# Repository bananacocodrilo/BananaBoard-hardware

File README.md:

# BananaBoard-hardware

This is still under development and subject to changes.

Split wireless keyboard based on the [mitosis](https://github.com/reversebias/mitosis-hardware) and the [chimera](https://github.com/GlenPickle/Chimera).

The goal is to make boards easy to solder and compatible with existing cases for popular keybards as "let's split" or "iris keyboard" and a miniboard for handwired builds.

I'll also publish a fork of their firmware as well since I need to use a matrix configuration instead of a "pin per switch", furthermore I'll add battery measure and underglow leds.

I haven't make a PCB in a while and is my first time using kicad so I'm learning as a I go.

Current state:
-
 - "Finished" schematic: I like how it is right now and it will probably stay like this.
 - "Finished" a first version for handwired builds (it fits in 24mmx50mm so I added 2 per board).
 - Second version of the 40% split PCB, I think is compatible with the "lets split" case but it isn't reversible so I'll need to create the "right hand" too.

Next steps: 
-
 - Decide a footprint for the switches (right now I'm not sure which footprint works with which switch).
 - (Currently working) Create the right hand of the lets split.
 - Investigate other lipo charger circuits. I've ordered a few cheap micro usb ones since I couldn't find reliable size info.
 - Start the firmware modifications.

Ortho 40% board (left hand):

Handwired keyboards board:

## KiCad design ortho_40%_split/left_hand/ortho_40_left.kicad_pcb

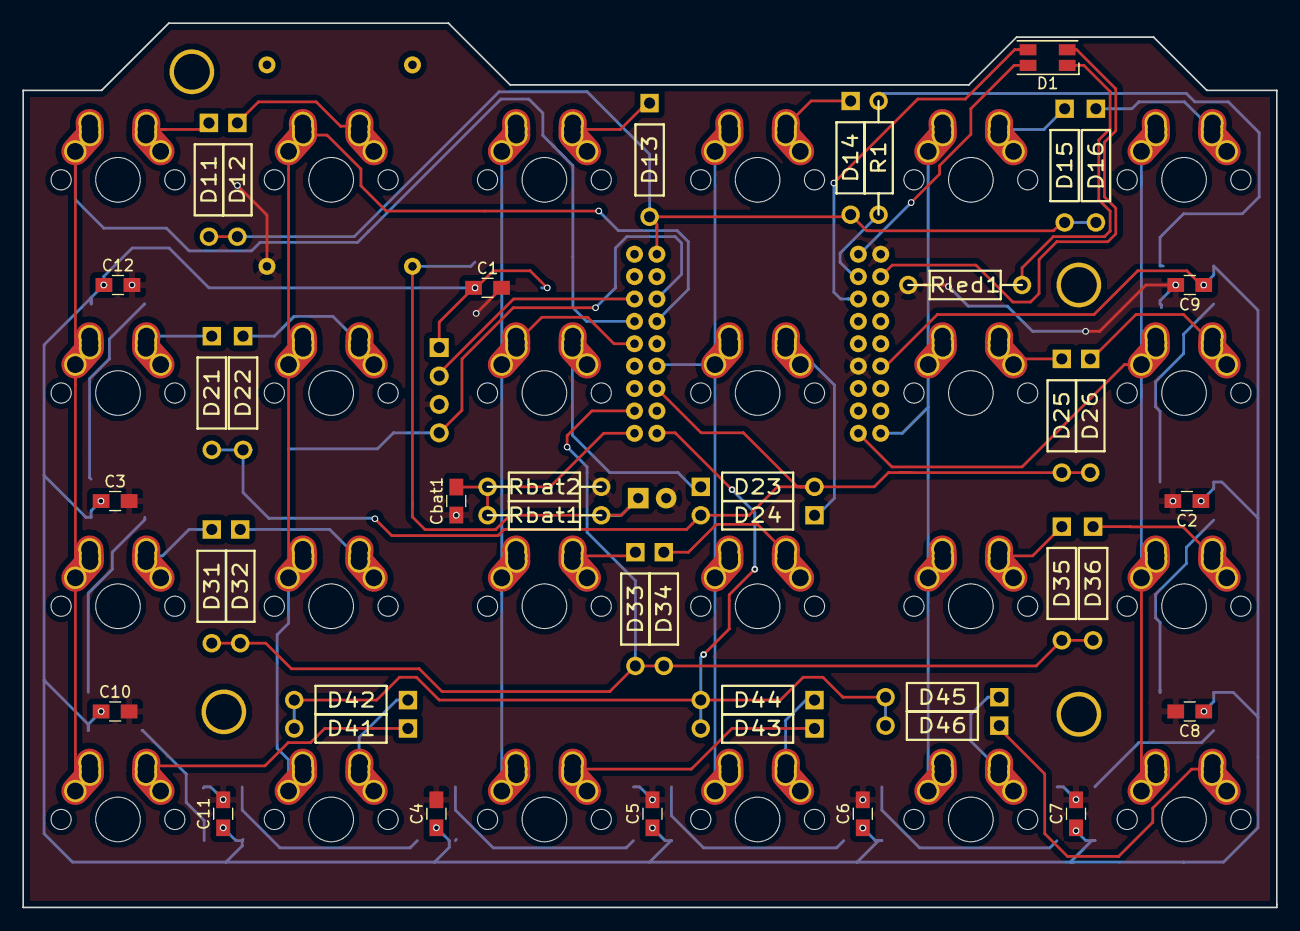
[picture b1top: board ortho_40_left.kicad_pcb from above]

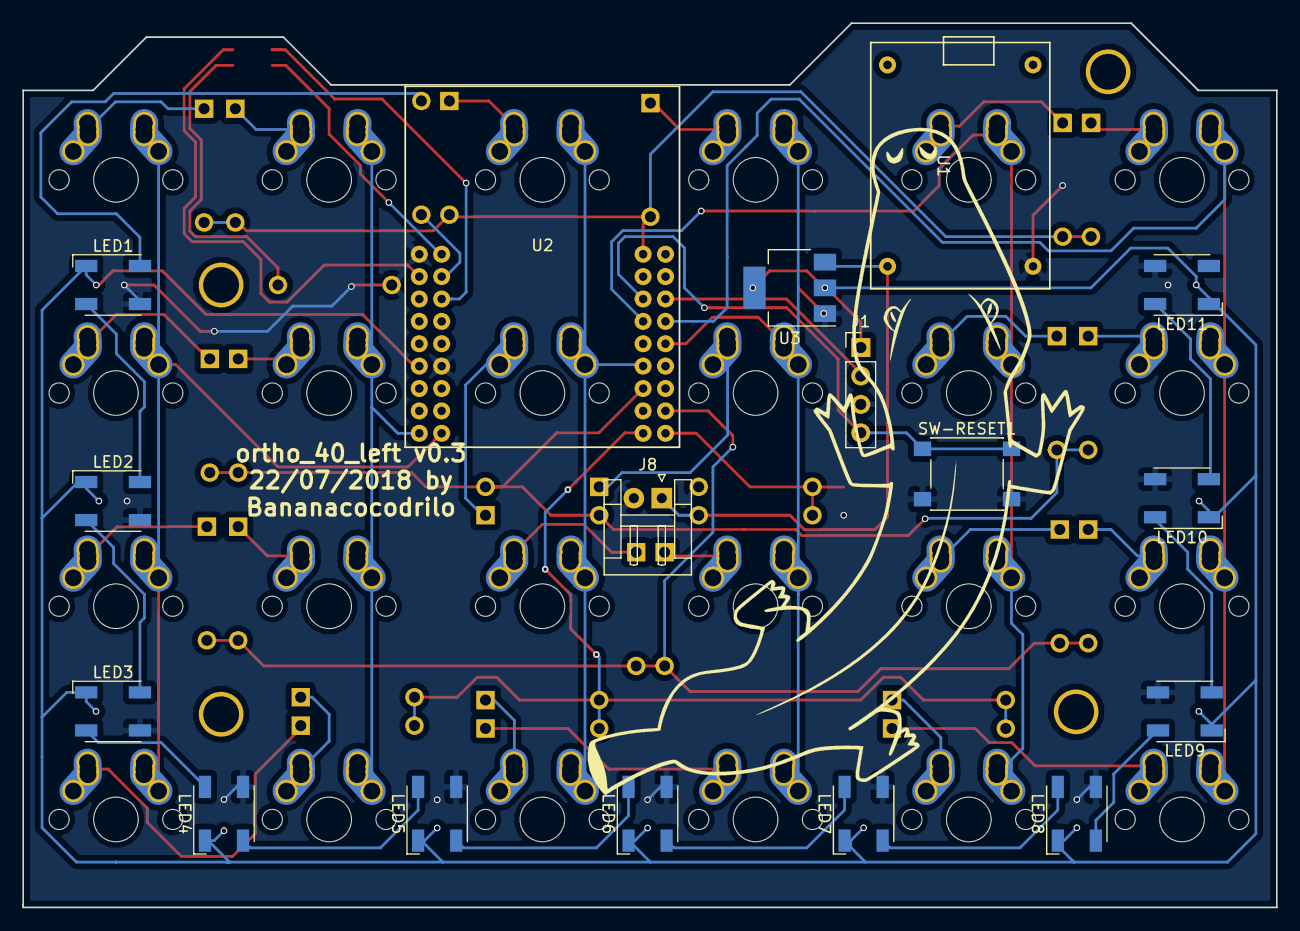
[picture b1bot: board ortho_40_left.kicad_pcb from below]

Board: 2 copper layers, 112.0 x 79.0 mm, 87 parts (17 on the bottom side), 56 nets.

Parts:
C1: 47uF; C_0805_HandSoldering
C2, C3, C4, C5, C6, C7, C8, C9, C10, C11, C12: 0.1uF; C_0805_HandSoldering
Cbat1: 22n; C_0805_HandSoldering
D1: LED_BAT; LED_RGB_1210
D11, D12, D13, D14, D15, D16, D21, D22, D23, D24, D25, D26, D31, D32, D33, D34, D35, D36, D41, D42, D43, D44, D45, D46: D; DIODE
J1: prog_pins; Pin_Header_Straight_1x04_Pitch2.54mm
J2, J3, J5, J7: Conn_01x01; HOLE_M3
J8: Conn-Battery; JST_EH_S02B-EH_02x2.50mm_Angled
K-11, K-12, K-13, K-14, K-15, K-16, K-21, K-22, K-23, K-24, K-25, K-26, K-31, K-32, K-33, K-34, K-35, K-36, K-41, K-42, K-43, K-44, K-45, K-46: KEYSW; Hybrid_PCB_100H_Dual_hole
LED1, LED2, LED3, LED4, LED5, LED6, LED7, LED8, LED9, LED10, LED11: WS2812B; LED_RGB_5050-4
R1: 470; RESISTOR
Rbat1: 10M; RESISTOR
Rbat2: 2.2M; RESISTOR
Rled1: 470; RESISTOR
SW-RESET1: SW_PUSH; SW_SPST_PTS645
U1: cargador-USB; cargador-mini-usb
U2: core51822; core51822-through-hole
U3: LM1117-3.3; SOT-223-3_TabPin2

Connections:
BAT-M: Cbat1.2, Rbat1.1, Rbat2.2, U2.36
GND: C1.2, C2.2, C3.2, C4.2, C5.2, C6.2, C7.2, C8.2, C9.2, C10.2, C11.2, C12.2, Cbat1.1, J1.3, J8.2, LED1.3, LED2.3, LED3.3, LED4.3, LED5.3, LED6.3, LED7.3, LED8.3, LED9.3, LED10.3, LED11.3, Rbat2.1, Rled1.1, SW-RESET1.2, U1.3, U2.1, U2.12, U3.1
LED-B: D1.4, U2.2
LED-G: D1.3, U2.6
LED-R: D1.2, U2.3
unnamed: D1.1, Rled1.2
unnamed: D11.2, K-11.2
unnamed: D12.2, K-12.2
unnamed: D13.2, K-13.2
unnamed: D14.2, K-14.2
unnamed: D15.2, K-15.2
unnamed: D16.2, K-16.2
unnamed: D21.2, K-21.2
unnamed: D22.2, K-22.2
unnamed: D23.2, K-23.2
unnamed: D24.2, K-24.2
unnamed: D25.2, K-25.2
unnamed: D26.2, K-26.2
unnamed: D31.2, K-31.2
unnamed: D32.2, K-32.2
unnamed: D33.2, K-33.2
unnamed: D34.2, K-34.2
unnamed: D35.2, K-35.2
unnamed: D36.2, K-36.2
unnamed: D41.2, K-41.2
unnamed: D42.2, K-42.2
unnamed: D43.2, K-43.2
unnamed: D44.2, K-44.2
unnamed: D45.2, K-45.2
unnamed: D46.2, K-46.2
unnamed: J1.2, U2.24
unnamed: J1.4, SW-RESET1.1, U2.23
unnamed: J8.1, Rbat1.2, U1.2, U3.3
unnamed: LED1.2, LED2.4
unnamed: LED1.4, R1.1
unnamed: LED2.2, LED3.4
unnamed: LED3.2, LED4.4
unnamed: LED4.2, LED5.4
unnamed: LED5.2, LED6.4
unnamed: LED6.2, LED7.4
unnamed: LED7.2, LED8.4
unnamed: LED8.2, LED9.4
unnamed: LED10.2, LED11.4
VCC: C1.1, C2.1, C3.1, C4.1, C5.1, C6.1, C7.1, C8.1, C9.1, C10.1, C11.1, C12.1, J1.1, LED1.1, LED2.1, LED3.1, LED4.1, LED5.1, LED6.1, LED7.1, LED8.1, LED9.1, LED10.1, LED11.1, U2.11, U3.2
col-1: K-11.1, K-21.1, K-31.1, K-41.1, U2.26
col-2: K-12.1, K-22.1, K-32.1, K-42.1, U2.25
col-3: K-13.1, K-23.1, K-33.1, K-43.1, U2.28
col-4: K-14.1, K-24.1, K-34.1, K-44.1, U2.29
col-5: K-15.1, K-25.1, K-35.1, K-45.1, U2.17
col-6: K-16.1, K-26.1, K-36.1, K-46.1, U2.18
row-1: D11.1, D12.1, D13.1, D14.1, D15.1, D16.1, U2.19
row-2: D21.1, D22.1, D23.1, D24.1, D25.1, D26.1, U2.31
row-3: D31.1, D32.1, D33.1, D34.1, D35.1, D36.1, U2.34
row-4: D41.1, D42.1, D43.1, D44.1, D45.1, D46.1, U2.35
underglow: R1.2, U2.4
underglowAux: LED9.2, LED10.4

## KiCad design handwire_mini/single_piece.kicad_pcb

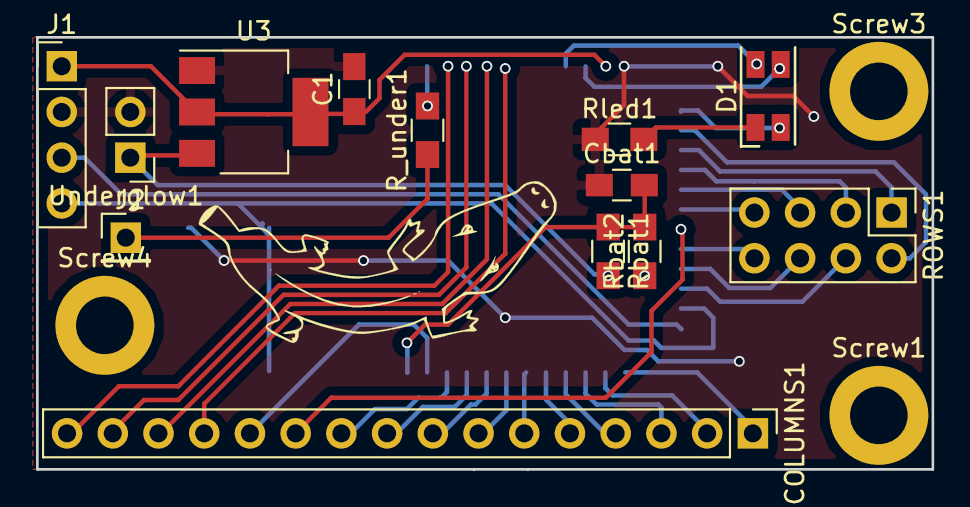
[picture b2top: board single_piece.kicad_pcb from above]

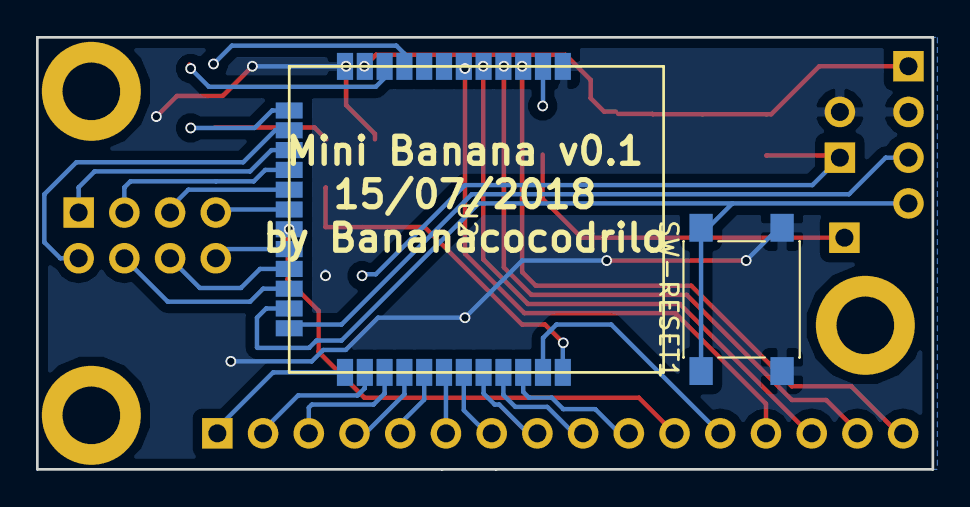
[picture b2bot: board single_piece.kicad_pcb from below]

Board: 2 copper layers, 49.8 x 24.0 mm, 18 parts (2 on the bottom side), 36 nets.

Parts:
C1: 47uF; C_0805_HandSoldering
COLUMNS1: Pin_Header_Straight_1x16_Pitch2.54mm
Cbat1: 22n; C_0805_HandSoldering
D1: LED_BAT; LED_RGB_1210
J1: prog_pins; Pin_Header_Straight_1x04_Pitch2.54mm
J2: Lipo; Pin_Header_Straight_1x02_Pitch2.54mm
ROWS1: ROWS; Pin_Header_Straight_2x04_Pitch2.54mm
R_under1: 470; R_0805_HandSoldering
Rbat1: 10M; R_0805_HandSoldering
Rbat2: 2.2M; R_0805_HandSoldering
Rled1: 470; R_0805_HandSoldering
SW-RESET1: SW_PUSH; SW_SPST_PTS645
Screw1, Screw3, Screw4: Screw; MountingHole_3.2mm_M3_ISO14580_Pad
U2: core51822; cpre51822-smd
U3: LM1117-3.3; SOT-223-3_TabPin2
Underglow1: TO_WS2812b; Pin_Header_Straight_1x01_Pitch2.54mm

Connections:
BAT-M: Cbat1.2, Rbat1.1, Rbat2.2, U2.36
COL-13: COLUMNS1.13, U2.6
COL-14: COLUMNS1.14, U2.5
COL-15: COLUMNS1.15, U2.4
COL-16: COLUMNS1.16, U2.3
GND: C1.2, Cbat1.1, J1.2, J2.2, Rbat2.1, Rled1.1, SW-RESET1.2, U2.1, U2.12, U3.1
LED-B: D1.3, U2.10
LED-G: D1.4, U2.9
LED-R: D1.2, U2.13
unnamed: COLUMNS1.1, U2.25
unnamed: COLUMNS1.2, U2.26
unnamed: COLUMNS1.3, U2.27
unnamed: COLUMNS1.4, U2.28
unnamed: COLUMNS1.5, U2.29
unnamed: COLUMNS1.6, U2.30
unnamed: COLUMNS1.7, U2.31
unnamed: COLUMNS1.8, U2.32
unnamed: COLUMNS1.9, U2.33
unnamed: COLUMNS1.10, U2.34
unnamed: COLUMNS1.12, U2.35
unnamed: D1.1, Rled1.2
unnamed: J1.3, U2.24
unnamed: J1.4, SW-RESET1.1, U2.23
unnamed: J2.1, Rbat1.2, U3.3
unnamed: R_under1.1, Underglow1.1
unnamed: R_under1.2, U2.2
VCC: C1.1, J1.1, U2.11, U3.2
col-11: COLUMNS1.11, U2.19
row1: ROWS1.1, U2.15
row2: ROWS1.2, U2.14
row3: ROWS1.3, U2.16
row4: ROWS1.4, U2.22
row5: ROWS1.5, U2.17
row6: ROWS1.8, U2.20
row7: ROWS1.7, U2.18
row8: ROWS1.6, U2.21

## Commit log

2018-07-08 Firts version
    Finished untested version.
    DRC pases ok
2018-07-08 Moved screw hole
2018-07-08 added images folder, moved diode and mounting hole
2018-07-15 Many changes, see desc
    Moved previous board to ortho_40% folder, also created a new board for handwired builds.
    Now working in modifying the ortho board to be compatible with the lets split cases
2018-07-15 updated readme, added image
2018-07-17 added gerber files
2018-07-18 updated pcb to fit lets split case
    I moved the files into a new folder "left" since it looks that it wont be fully compatible with the case thus I'll need to create another version for the right hand
2018-07-22 working on right hand
